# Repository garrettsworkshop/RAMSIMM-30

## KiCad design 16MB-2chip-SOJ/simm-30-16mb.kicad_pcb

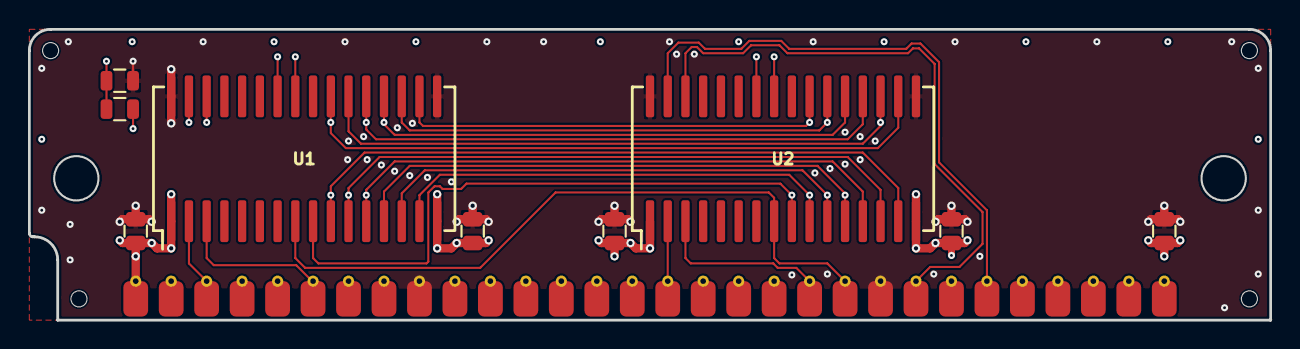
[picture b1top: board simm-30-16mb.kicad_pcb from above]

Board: 4 copper layers, 88.9 x 20.8 mm, 14 parts (0 on the bottom side), 26 nets.

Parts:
C1, C2, C3, C4, C5: 100n; C_0805
H1, H2, H3, H4: MountingHole; PasteHole_1.152mm_NPTH
J1: DRAM-SIMM-30; SIMM-30_Edge
R1: EDO; R_0805
R2: FPM; R_0805
U1, U2: KM44C16104; SOJ-32-400mil-Skinny

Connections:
+5V: C1.1, C2.1, C3.1, C4.1, C5.1, J1.1, J1.30, U1.1, U1.16, U2.1, U2.16
/1A0: J1.4, U1.10, U2.15
/1A1: J1.5, U1.11, U2.14
/1A2: J1.7, U1.12, U2.13
/1A3: J1.24, U1.13, U2.12
/1A4: J1.19, U1.14, U2.11
/1A5: J1.18, U1.15, U2.10
/1A6: J1.14, U1.18, U2.23
/1A7: J1.15, U1.19, U2.22
/1A8: J1.12, U1.20, U2.21
/1A9: J1.11, U1.21, U2.20
/1A10: J1.17, U1.22, U2.19
/1A11: J1.8, U1.23, U2.18
/D0: J1.3, U1.2
/D1: J1.6, U1.3
/D2: J1.10, U1.30
/D3: J1.13, U1.31
/D4: J1.16, U2.2
/D5: J1.20, U2.3
/D6: J1.23, U2.30
/D7: J1.25, U2.31
/~CAS~: J1.2, R1.1, U1.26, U2.26
/~OE~: R1.2, R2.1, U1.25, U2.25
/~RAS~: J1.27, U1.9, U2.9
/~WE~: J1.21, U1.8, U2.8
GND: C1.2, C2.2, C3.2, C4.2, C5.2, J1.9, J1.22, R2.2, U1.17, U1.32, U2.17, U2.32

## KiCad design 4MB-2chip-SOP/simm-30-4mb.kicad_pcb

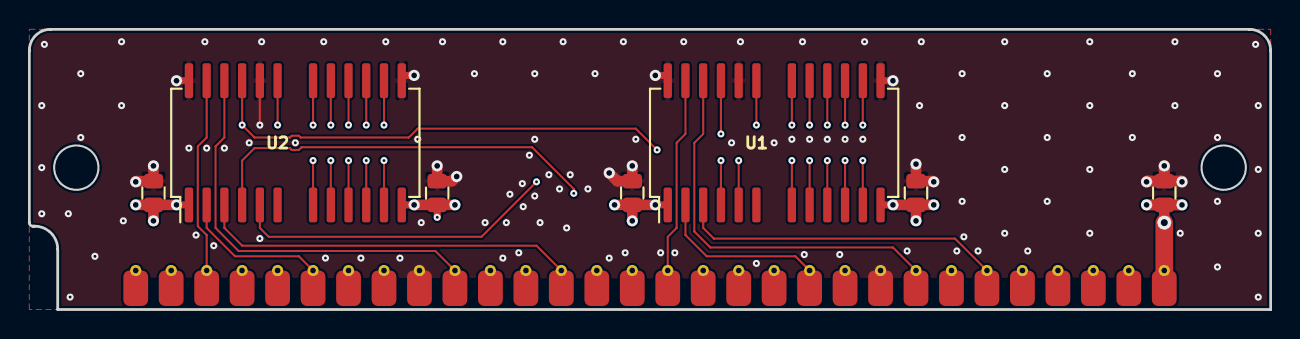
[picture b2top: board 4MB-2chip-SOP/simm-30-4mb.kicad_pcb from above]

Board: 4 copper layers, 88.9 x 20.1 mm, 8 parts (0 on the bottom side), 24 nets.

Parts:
C1, C2, C3, C4, C5: 100n; C_0805
J1: DRAM-SIMM-30; SIMM-30_Edge
U1, U2: AS4C4M4; SOP-24-26-300mil

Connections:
+5V: C1.1, C2.1, C3.1, C4.1, C5.1, J1.1, J1.30, U1.1, U1.13, U2.1, U2.13
/1A0: J1.15, U1.9, U2.11
/1A1: J1.12, U1.10, U2.10
/1A2: J1.8, U1.11, U2.9
/1A3: J1.5, U1.12, U2.8
/1A4: J1.4, U1.15, U2.21
/1A5: J1.7, U1.16, U2.19
/1A6: J1.11, U1.17, U2.18
/1A7: J1.14, U1.18, U2.17
/1A8: J1.17, U1.19, U2.16
/1A9: J1.19, U1.21, U2.15
/1A10: J1.18, U1.8, U2.12
/D0: J1.3, U2.25
/D1: J1.6, U2.2
/D2: J1.10, U2.24
/D3: J1.13, U2.3
/D4: J1.16, U1.25
/D5: J1.20, U1.2
/D6: J1.23, U1.24
/D7: J1.25, U1.3
/~CAS~: J1.2, U1.23, U2.23
/~RAS~: J1.27, U1.5, U2.5
/~WE~: J1.21, U1.4, U2.4
GND: C1.2, C2.2, C3.2, C4.2, C5.2, J1.9, J1.22, U1.14, U1.22, U1.26, U2.14, U2.22, U2.26

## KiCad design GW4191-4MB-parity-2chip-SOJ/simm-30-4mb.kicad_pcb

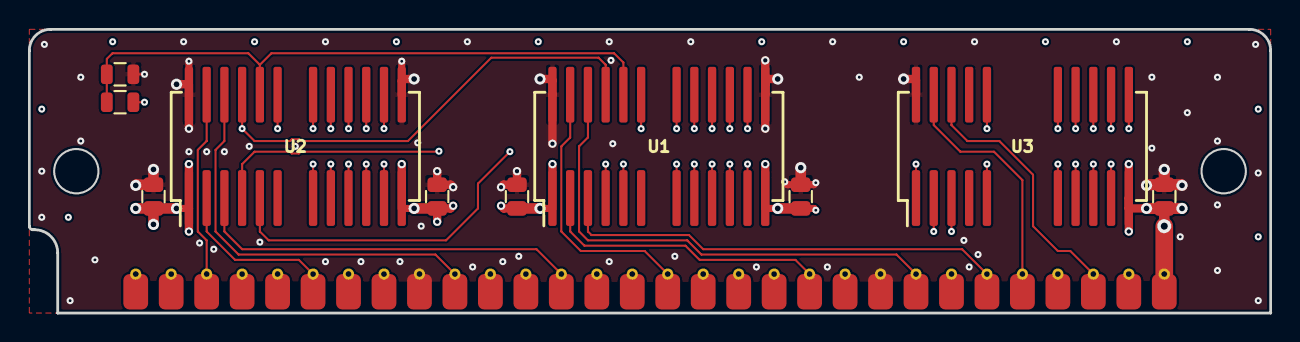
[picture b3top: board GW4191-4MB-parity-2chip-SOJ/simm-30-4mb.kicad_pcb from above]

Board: 4 copper layers, 88.9 x 20.3 mm, 11 parts (0 on the bottom side), 28 nets.

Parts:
C1, C2, C3, C4, C5: 100n; C_0805
J1: DRAM-SIMM-30; SIMM-30_Edge
R1: EDO; R_0805
R2: FPM; R_0805
U1, U2: AS4C4M4; SOJ-24-26-300mil
U3: AS4C4M4; SOJ-20-26-300mil

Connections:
+5V: C1.1, C2.1, C3.1, C4.1, C5.1, J1.1, J1.30, U1.1, U1.13, U2.1, U2.13, U3.13
/1A0: J1.15, U1.9, U2.11, U3.9
/1A1: J1.12, U1.10, U2.10, U3.10
/1A2: J1.8, U1.11, U2.9, U3.11
/1A3: J1.5, U1.12, U2.8, U3.12
/1A4: J1.4, U1.15, U2.21, U3.14
/1A5: J1.7, U1.16, U2.19, U3.15
/1A6: J1.11, U1.17, U2.18, U3.16
/1A7: J1.14, U1.18, U2.17, U3.17
/1A8: J1.17, U1.19, U2.16, U3.18
/1A9: J1.19, U1.21, U2.15, U3.5
/1A10: J1.18, U1.8, U2.12, U3.22
/D0: J1.3, U2.25
/D1: J1.6, U2.2
/D2: J1.10, U2.24
/D3: J1.13, U2.3
/D4: J1.16, U1.25
/D5: J1.20, U1.2
/D6: J1.23, U1.24
/D7: J1.25, U1.3
/DP: J1.29, U3.1
/QP: J1.26, U3.25
/~CASP~: J1.28, U3.24
/~CAS~: J1.2, R1.1, U1.23, U2.23
/~OE~: R1.2, R2.1, U1.22, U2.22
/~RAS~: J1.27, U1.5, U2.5, U3.3
/~WE~: J1.21, U1.4, U2.4, U3.2
GND: C1.2, C2.2, C3.2, C4.2, C5.2, J1.9, J1.22, R2.2, U1.14, U1.26, U2.14, U2.26, U3.26
